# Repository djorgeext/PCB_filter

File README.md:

PCB para filtrado de PCG usando un sensor PZT.

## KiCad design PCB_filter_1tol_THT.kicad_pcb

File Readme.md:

PCB con amplificador - filtro para señal acústica de un sensor piezoeléctrico.

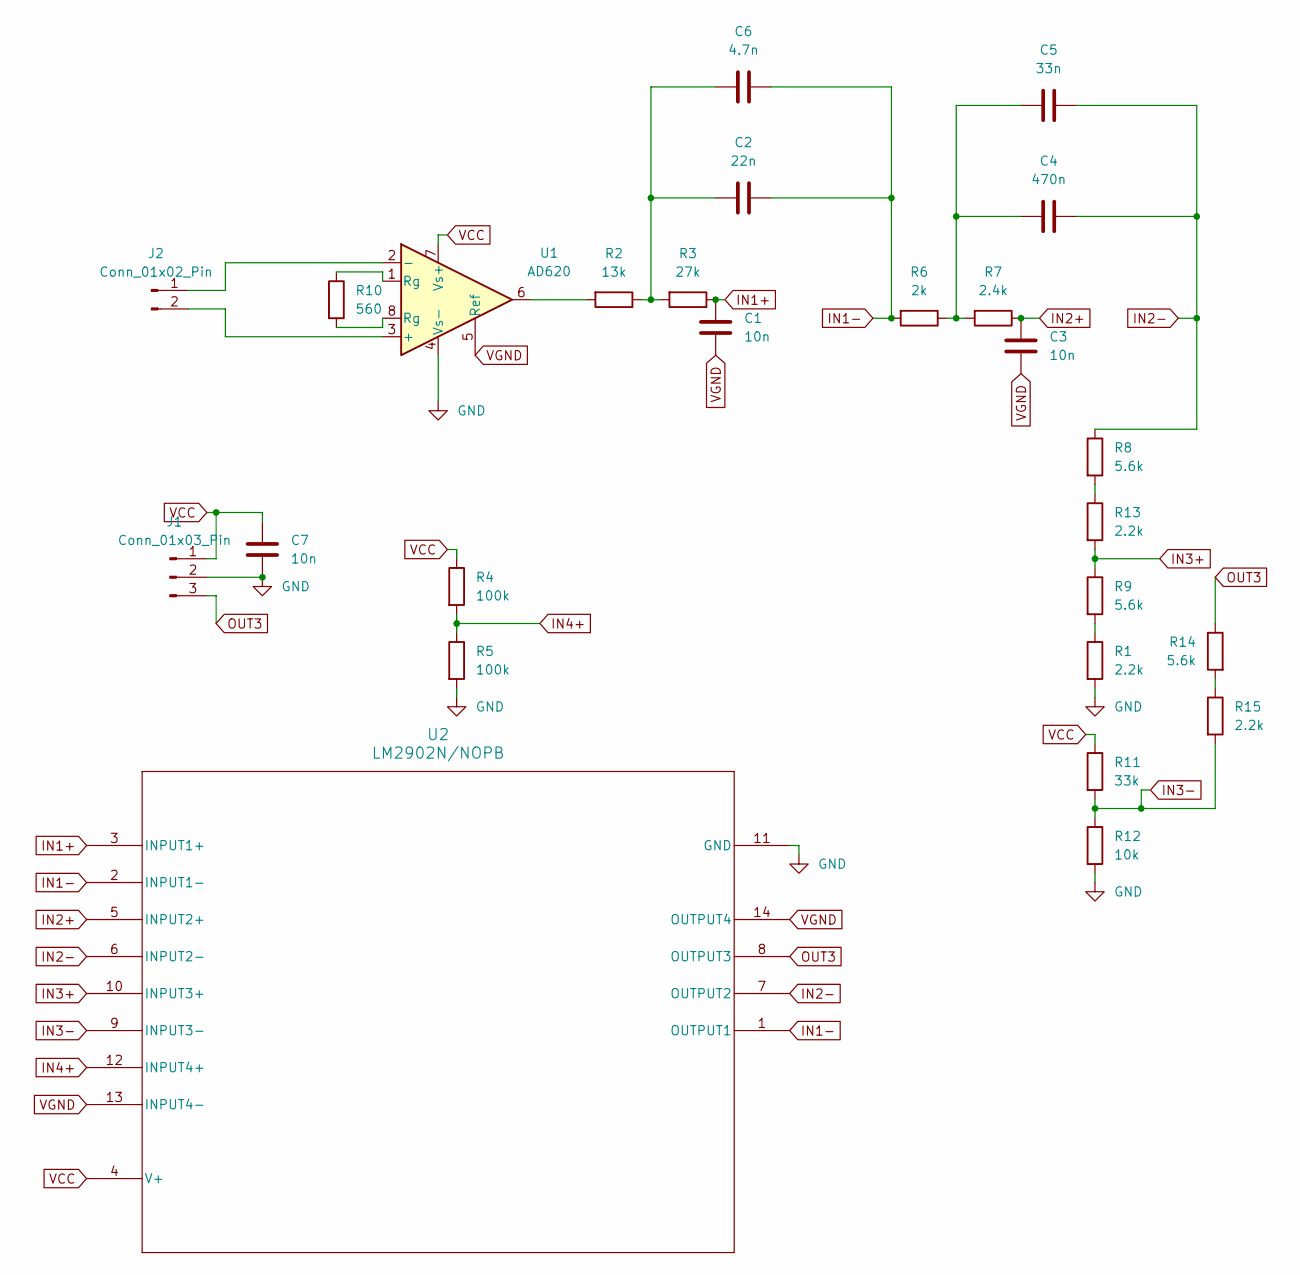
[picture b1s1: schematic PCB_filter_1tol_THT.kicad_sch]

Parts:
C1, C3, C7: 10n; C_Disc_D5.0mm_W2.5mm_P2.50mm
C2: 22n; C_Disc_D5.0mm_W2.5mm_P2.50mm
C4: 470n; C_Disc_D11.0mm_W5.0mm_P10.00mm
C5: 33n; C_Disc_D5.0mm_W2.5mm_P2.50mm
C6: 4.7n; C_Disc_D5.0mm_W2.5mm_P2.50mm
J1: Conn_01x03_Pin; SolderWire-0.1sqmm_1x03_P3.6mm_D0.4mm_OD1mm_Relief
J2: Conn_01x02_Pin; SolderWire-0.1sqmm_1x02_P3.6mm_D0.4mm_OD1mm_Relief
R1, R13, R15: 2.2k; R_hueco_grande
R2: 13k; R_hueco_grande
R3: 27k; R_hueco_grande
R4, R5: 100k; R_hueco_grande
R6: 2k; R_hueco_grande
R7: 2.4k; R_hueco_grande
R8, R9, R14: 5.6k; R_hueco_grande
R10: 560; R_hueco_grande
R11: 33k; R_hueco_grande
R12: 10k; R_hueco_grande
U1: AD620; DIP-8_W7.62mm_Socket
U2: LM2902N/NOPB; NFF_14

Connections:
GND: C7.2, J1.2, R1.2, R5.2, R12.2, U1.4 (Vs-), U2.11 (GND)
IN1+: C1.1, R3.1, U2.3 (INPUT1+)
IN1-: C2.1, C6.1, R6.2, U2.1 (OUTPUT1), U2.2 (INPUT1-)
IN2+: C3.1, R7.1, U2.5 (INPUT2+)
IN2-: C4.1, C5.1, R8.1, U2.6 (INPUT2-), U2.7 (OUTPUT2)
IN3+: R9.1, R13.2, U2.10 (INPUT3+)
IN3-: R11.2, R12.1, R15.2, U2.9 (INPUT3-)
IN4+: R4.2, R5.1, U2.12 (INPUT4+)
unnamed: C2.2, C6.2, R2.1, R3.2
unnamed: C4.2, C5.2, R6.1, R7.2
unnamed: J2.1, U1.2 (-)
unnamed: J2.2, U1.3 (+)
unnamed: R1.1, R9.2
unnamed: R2.2, U1.6
unnamed: R10.1, U1.1 (Rg)
unnamed: R10.2, U1.8 (Rg)
unnamed: R8.2, R13.1
unnamed: R14.2, R15.1
OUT3: J1.3, R14.1, U2.8 (OUTPUT3)
VCC: C7.1, J1.1, R4.1, R11.1, U1.7 (Vs+), U2.4 (V+)
VGND: C1.2, C3.2, U1.5 (Ref), U2.13 (INPUT4-), U2.14 (OUTPUT4)

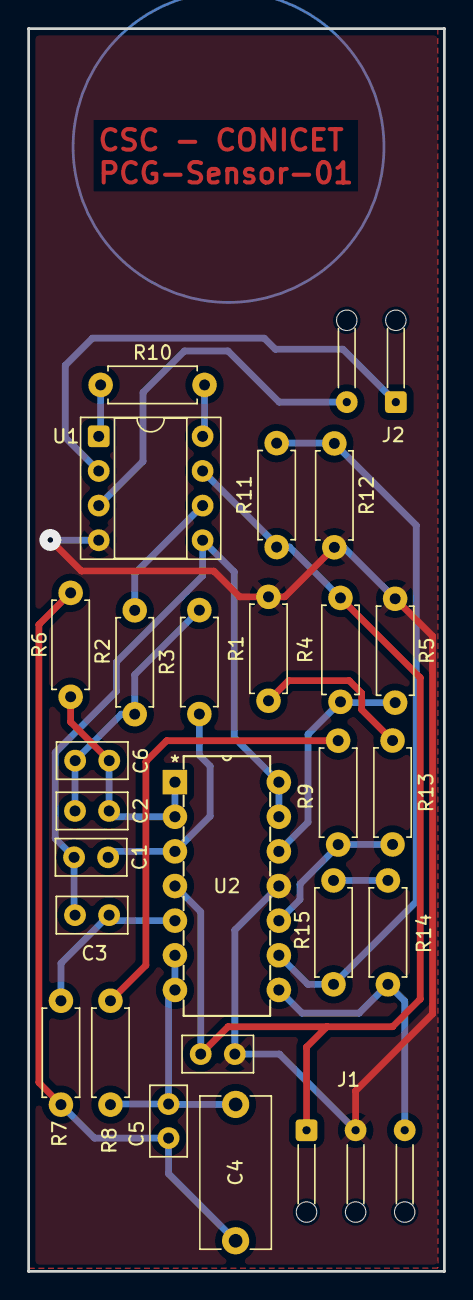
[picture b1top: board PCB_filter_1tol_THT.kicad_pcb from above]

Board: 2 copper layers, 30.5 x 91.1 mm, 26 parts (0 on the bottom side), 21 nets.

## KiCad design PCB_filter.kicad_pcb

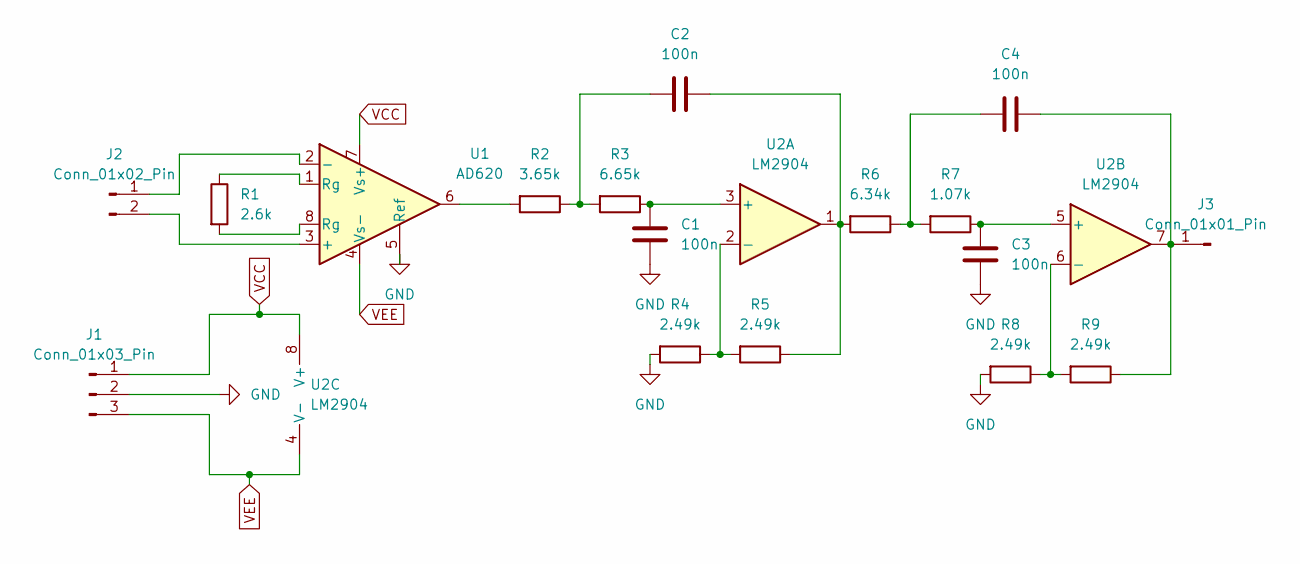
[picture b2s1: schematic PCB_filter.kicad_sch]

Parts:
C1, C2, C3, C4: 100n; C_Disc_D5.0mm_W2.5mm_P2.50mm
J1: Conn_01x03_Pin; PinHeader_1x03_P2.54mm_Vertical
J2: Conn_01x02_Pin; PinHeader_1x02_P2.54mm_Vertical
J3: Conn_01x01_Pin; PinHeader_1x01_P2.54mm_Vertical
R1: 2.6k; R_Axial_DIN0207_L6.3mm_D2.5mm_P7.62mm_Horizontal
R2: 3.65k; R_Axial_DIN0207_L6.3mm_D2.5mm_P7.62mm_Horizontal
R3: 6.65k; R_Axial_DIN0207_L6.3mm_D2.5mm_P7.62mm_Horizontal
R4, R5, R8, R9: 2.49k; R_Axial_DIN0207_L6.3mm_D2.5mm_P7.62mm_Horizontal
R6: 6.34k; R_Axial_DIN0207_L6.3mm_D2.5mm_P7.62mm_Horizontal
R7: 1.07k; R_Axial_DIN0207_L6.3mm_D2.5mm_P7.62mm_Horizontal
U1: AD620; DIP-8_W7.62mm_Socket
U2: LM2904; DIP-8_W7.62mm_Socket

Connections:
GND: C1.2, C3.2, J1.2, R4.2, R8.2, U1.5 (Ref)
unnamed: C2.1, R5.1, R6.2, U2.1
unnamed: C2.2, R2.1, R3.2
unnamed: C4.2, R6.1, R7.2
unnamed: J2.1, U1.2 (-)
unnamed: J2.2, U1.3 (+)
unnamed: C4.1, J3.1, R9.1, U2.7
unnamed: R1.1, U1.1 (Rg)
unnamed: R1.2, U1.8 (Rg)
unnamed: R2.2, U1.6
unnamed: C1.1, R3.1, U2.3 (+)
unnamed: R4.1, R5.2, U2.2 (-)
unnamed: C3.1, R7.1, U2.5 (+)
unnamed: R8.1, R9.2, U2.6 (-)
VCC: J1.1, U1.7 (Vs+), U2.8 (V+)
VEE: J1.3, U1.4 (Vs-), U2.4 (V-)

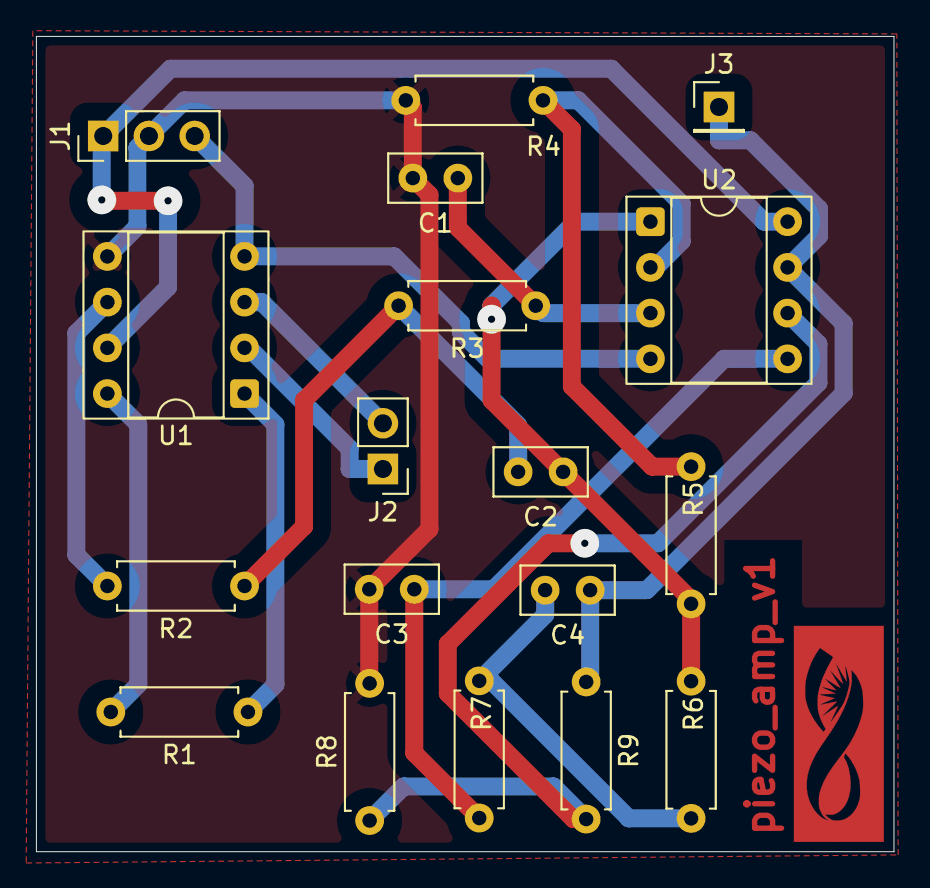
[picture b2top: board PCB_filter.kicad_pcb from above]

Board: 2 copper layers, 47.6 x 45.3 mm, 19 parts (0 on the bottom side), 16 nets.

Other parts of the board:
Ref**: Val**; LogoConicetInvertido

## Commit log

2025-08-07 PCB para filtrado
2025-10-14 last
2025-11-17 Add project description to README
